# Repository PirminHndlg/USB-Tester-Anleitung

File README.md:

<h1>Anleitung zum USB Tester Löt Kit</h1>

<div class="img-container">
    
</div>

<h4>Enthaltene Komponenten</h4>
<ul>
    <li>1x pcb</li>
    <li>2x USB Typ-C Buchse (teilweise schon an pcb angelötet)</li>
    <li>1x USB Typ-A 3.0 Buchse</li>
    <li>1x Micro USB Typ-B Buchse</li>
    <li>1x Mini USB Typ-B Buchse</li>
    <li>1x USB Typ-B 3.0 Buchse</li>
    <li>1x Batterie Halterung</li>
    <li>30x Widerstand 2.2kΩ (25 + 5 Reserve)</li>
    <li>30x LEDs gelb (25 + 5 Reserve)</li>
    <li>1x Kondensator 10μF</li>
</ul>

<div class="img-container">
    
</div>

<p style="background-color: green; padding: 10px"><strong>Hinweis:</strong> Bei der USB-C Buchse auf der rechten Seite
    kann es sein, dass sich einige Pins untereinander brücken. Das ist kein Problem! Die Kontakte auf dem pcb sind
    sowieso mit einer VCC-Plane verbunden. Auf der linken Seite darf es aber nicht sein!</p>

<h4>Anleitung</h4>
<ol>
    <li>
        Löte die Widerstände und die LEDs auf die Platine, die oberen Kontakte sind für die Widerstände und die
        unteren für die LEDs
        <p style="background-color: red; padding: 10px"><strong>Wichtig:</strong> die LEDs haben eine Ausrichtung!</p>
        <div class="Website/img-container">
            
        </div>
        Auf der Rückseite der LED sieht man eine Markierung für die Kontakte. Der Kontakt mit dem Kreuz ist der Minuspol
        und muss an den linken Kontakt der Platine mit der vollständigen Umrandung gelötet werden.
        <div class="Website/img-container">
            
        </div>
        Auf der Vorderseite ist die Unterscheidung der beiden Kontakte der LEDs leider nur schwer zu erkennen, aber der
        Pluspol hat zwei kleine Streifen und der Minuspol nur einen.
        <br><br>
        12 LEDs + Widerstände sind für die linke Seite der Platine und 12 für die rechte Seite bestimmt. Das letze Paar
        kommt unten in die linke Ecke der Platine bei der Aufschrift "SHIELD".
    </li>
    <li>
        Löte die Buchsen auf die Platine. Anordnung siehe Bild. Für die Stecker auf der rechten Seite spielt es
        keine Rolle, ob einzelne Kontakte sich untereinander berühren und einen Kurzschluss bilden.
        <div class="img-container">

        </div>
        Falls die USB-C Buchsen noch nicht angelötet sind, ist das der schwierigste Teil. Ich war am erfolgreichsten,
        indem ich die mit Reflow-Löten angelötet habe.
        <p style="background-color: orange; padding: 10px"><strong>Hinweis:</strong> Bei der Micro-USB-B-Buche habe ich einen kleinen Fehler beim pcb gemacht. Diese muss sich das eine Bein mit einer USB-C-Buchse teilen. Gequetscht sollte aber alles nebeneinander passen.</p>
    </li>
    <li>
        Löte den Kondensator an die richtige Stelle neben dem Pluspol der Batterie. Die Ausrichtung spielt keine Rolle.
        <div class="img-container">
            
        </div>
    </li>
    <li>
        Löte die Batterie-Halterung an. Achte auf die richtige Polung! Es gibt eine kleine Markierung an der Ecke der
        Halterung für den Plus- und Minuspol.
    </li>
    <li>
        Und fertig ist dein USB Tester! Viel Spass beim Testen von USB-Kabeln!
    </li>
</ol>

<h3 style="background-color: red; text-align: center; padding: 10px; border-radius: 10px">Wie es auch überall steht, ist es wichtig, dass man
    den Tester <strong>nicht</strong> an ein Gerät anschließt,
    sondern nur Kabel!</h3>

<div class="img-container">
    
</div>

<h4>Weitere Links</h4>

<p><a href="https://github.com/PirminHndlg/USB-Tester-Anleitung/tree/main/Case">Hier</a> gibt eine 3D-Druck-Vorlage für
    ein kleines, einfaches Case.</p>

<p><a href="https://github.com/PirminHndlg/USB-Tester-Anleitung/tree/main/pcb">Hier</a> kann man das KiCad-Projekt zum
    pcb finden. Ich habe das <a href="https://github.com/alvarop/usb_c_cable_tester">Original von alvarop</a> etwas
    angepasst, da einzelne Teile nicht mehr verfügbar waren. Eine aktuelle Liste gibt es <a
            href="https://github.com/PirminHndlg/USB-Tester-Anleitung/blob/main/pcb/LCSC%20Exported%20May%2030%202024.csv">hier</a>
</p>

<h4>Erklärung zur Pin-Belegung</h4>

<div class="table-container">
    <table>
        <tr>
            <th>Charge only</th>
            <td>GND</td>
            <td>VBUS</td>
        </tr>
        <tr>
            <th>USB 2.0</th>
            <td>GND</td>
            <td>VBUS</td>
            <td>D-</td>
            <td>D+</td>
        </tr>
        <tr>
            <th>USB 3.0</th>
            <td>GND</td>
            <td>VBUS</td>
            <td>D-</td>
            <td>D+</td>
            <td>RX-</td>
            <td>RX+</td>
            <td>TX-</td>
            <td>TX+</td>
        </tr>
    </table>
</div>
<p>Bei USB-C als Host (Buchse auf linker Seite) und Client (Buchse auf rechter Seite) leuchten beide Seiten, da dann
    sowohl die A als auch die B Pins verbunden sind. Außerdem sollte mind. ein CC-Pin verbunden sein</p>

<div class="img-container">
    
</div>

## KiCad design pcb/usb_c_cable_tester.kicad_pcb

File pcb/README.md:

[gbr.zip](gbr.zip) für pcb-Bestellung

[components_lcsc.csv](components_lcsc.csv) enthält den Einkaufswagen bei LCSC für 50 USB-Tester

[kicad](kicad)-Ordner mit Kicad-Projekt

Kosten für 50 Stück: ca. 180€ (inkl. Versand) &#8594; unter 4€/Stück

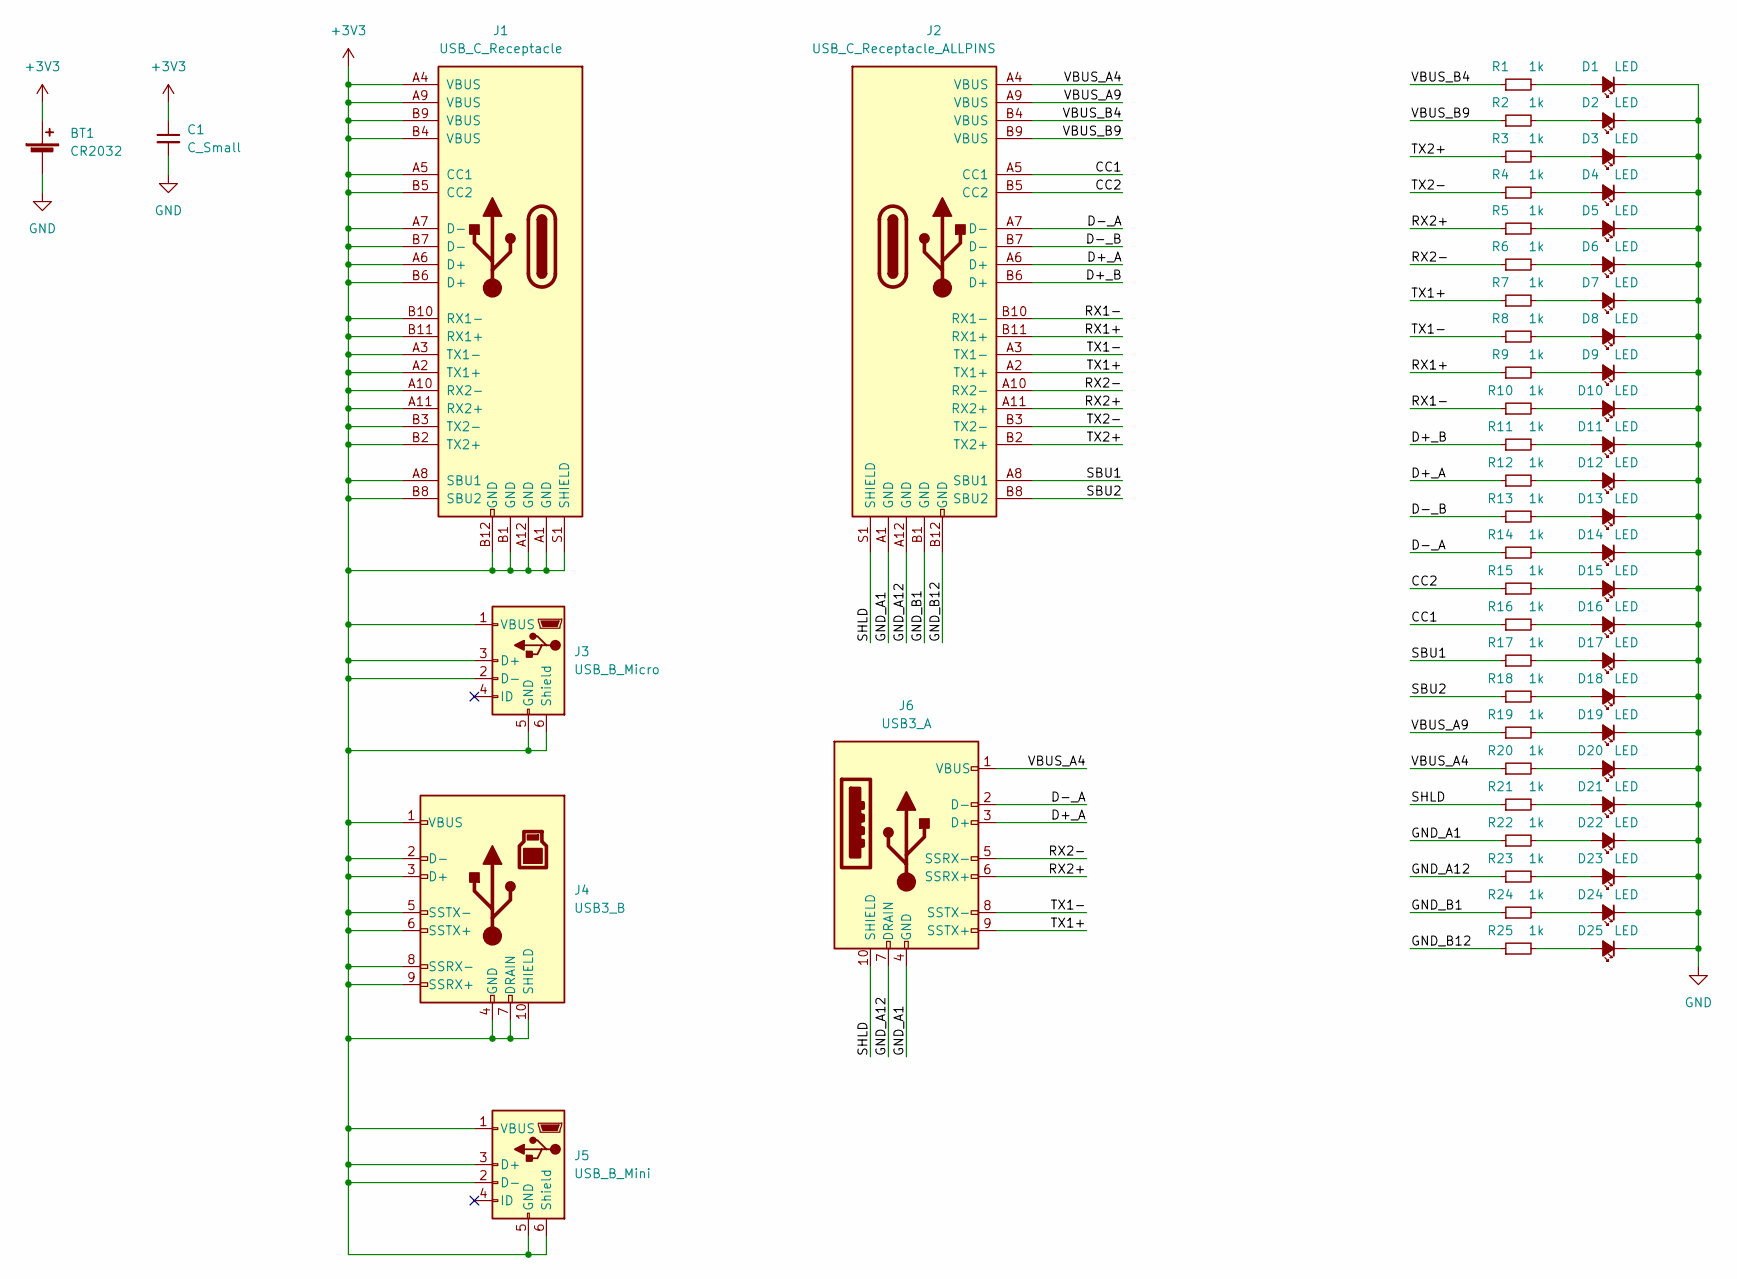
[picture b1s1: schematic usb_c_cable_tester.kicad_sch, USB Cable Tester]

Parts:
BT1: CR2032; BAT-TH_CR2032-BS-6-1; LCSC C70377
C1: C_Small; C_0805_2012Metric; LCSC C15850
D1, D2, D3, D4, D5, D6, D7, D8, D9, D10, D11, D12, D13, D14, D15, D16, D17, D18, D19, D20, D21, D22, D23, D24, D25: LED; LED_0603_1608Metric; LCSC C72038
J1: USB_C_Receptacle; USB_C; LCSC C456013
J2: USB_C_Receptacle_ALLPINS; USB_C; LCSC C456013
J3: USB_B_Micro; MICRO-USB-SMD_10118194-0001LF; LCSC C132563
J4: USB3_B; USB-B-TH_XUNPU_USB-306BWD-ARW; LCSC C2895032
J5: USB_B_Mini; MINI-USB-SMD_MINI-5PTP; LCSC C2681563
J6: USB3_A; USB-A-TH_U231-091N-5; LCSC C381137
R1, R2, R3, R4, R5, R6, R7, R8, R9, R10, R11, R12, R13, R14, R15, R16, R17, R18, R19, R20, R21, R22, R23, R24, R25: 1k; R_0603_1608Metric; LCSC C4190

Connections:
+3V3: BT1.1 (+), C1.1, J1.A1 (GND), J1.A2 (TX1+), J1.A3 (TX1-), J1.A4 (VBUS), J1.A5 (CC1), J1.A6 (D+), J1.A7 (D-), J1.A8 (SBU1), J1.A9 (VBUS), J1.A10 (RX2-), J1.A11 (RX2+), J1.A12 (GND), J1.B1 (GND), J1.B2 (TX2+), J1.B3 (TX2-), J1.B4 (VBUS), J1.B5 (CC2), J1.B6 (D+), J1.B7 (D-), J1.B8 (SBU2), J1.B9 (VBUS), J1.B10 (RX1-), J1.B11 (RX1+), J1.B12 (GND), J1.S1 (SHIELD), J3.1 (VBUS), J3.2 (D-), J3.3 (D+), J3.5 (GND), J3.6 (Shield), J4.1 (VBUS), J4.2 (D-), J4.3 (D+), J4.4 (GND), J4.5 (SSTX-), J4.6 (SSTX+), J4.7 (DRAIN), J4.8 (SSRX-), J4.9 (SSRX+), J4.10 (SHIELD), J5.1 (VBUS), J5.2 (D-), J5.3 (D+), J5.5 (GND), J5.6 (Shield)
/CC1: J2.A5 (CC1), R16.1
/CC2: J2.B5 (CC2), R15.1
/D+_A: J2.A6 (D+), J6.3 (D+), R12.1
/D+_B: J2.B6 (D+), R11.1
/D-_A: J2.A7 (D-), J6.2 (D-), R14.1
/D-_B: J2.B7 (D-), R13.1
/GND_A1: J2.A1 (GND), J6.4 (GND), R22.1
/GND_A12: J2.A12 (GND), J6.7 (DRAIN), R23.1
/GND_B1: J2.B1 (GND), R24.1
/GND_B12: J2.B12 (GND), R25.1
/RX1+: J2.B11 (RX1+), R9.1
/RX1-: J2.B10 (RX1-), R10.1
/RX2+: J2.A11 (RX2+), J6.6 (SSRX+), R5.1
/RX2-: J2.A10 (RX2-), J6.5 (SSRX-), R6.1
/SBU1: J2.A8 (SBU1), R17.1
/SBU2: J2.B8 (SBU2), R18.1
/SHLD: J2.S1 (SHIELD), J6.10 (SHIELD), R21.1
/TX1+: J2.A2 (TX1+), J6.9 (SSTX+), R7.1
/TX1-: J2.A3 (TX1-), J6.8 (SSTX-), R8.1
/TX2+: J2.B2 (TX2+), R3.1
/TX2-: J2.B3 (TX2-), R4.1
/VBUS_A4: J2.A4 (VBUS), J6.1 (VBUS), R20.1
/VBUS_A9: J2.A9 (VBUS), R19.1
/VBUS_B4: J2.B4 (VBUS), R1.1
/VBUS_B9: J2.B9 (VBUS), R2.1
GND: BT1.2 (-), C1.2, D1.1 (K), D2.1 (K), D3.1 (K), D4.1 (K), D5.1 (K), D6.1 (K), D7.1 (K), D8.1 (K), D9.1 (K), D10.1 (K), D11.1 (K), D12.1 (K), D13.1 (K), D14.1 (K), D15.1 (K), D16.1 (K), D17.1 (K), D18.1 (K), D19.1 (K), D20.1 (K), D21.1 (K), D22.1 (K), D23.1 (K), D24.1 (K), D25.1 (K)
unnamed: D1.2 (A), R1.2
unnamed: D2.2 (A), R2.2
unnamed: D3.2 (A), R3.2
unnamed: D4.2 (A), R4.2
unnamed: D5.2 (A), R5.2
unnamed: D6.2 (A), R6.2
unnamed: D7.2 (A), R7.2
unnamed: D8.2 (A), R8.2
unnamed: D9.2 (A), R9.2
unnamed: D10.2 (A), R10.2
unnamed: D11.2 (A), R11.2
unnamed: D12.2 (A), R12.2
unnamed: D13.2 (A), R13.2
unnamed: D14.2 (A), R14.2
unnamed: D15.2 (A), R15.2
unnamed: D16.2 (A), R16.2
unnamed: D17.2 (A), R17.2
unnamed: D18.2 (A), R18.2
unnamed: D19.2 (A), R19.2
unnamed: D20.2 (A), R20.2
unnamed: D21.2 (A), R21.2
unnamed: D22.2 (A), R22.2
unnamed: D23.2 (A), R23.2
unnamed: D24.2 (A), R24.2
unnamed: D25.2 (A), R25.2

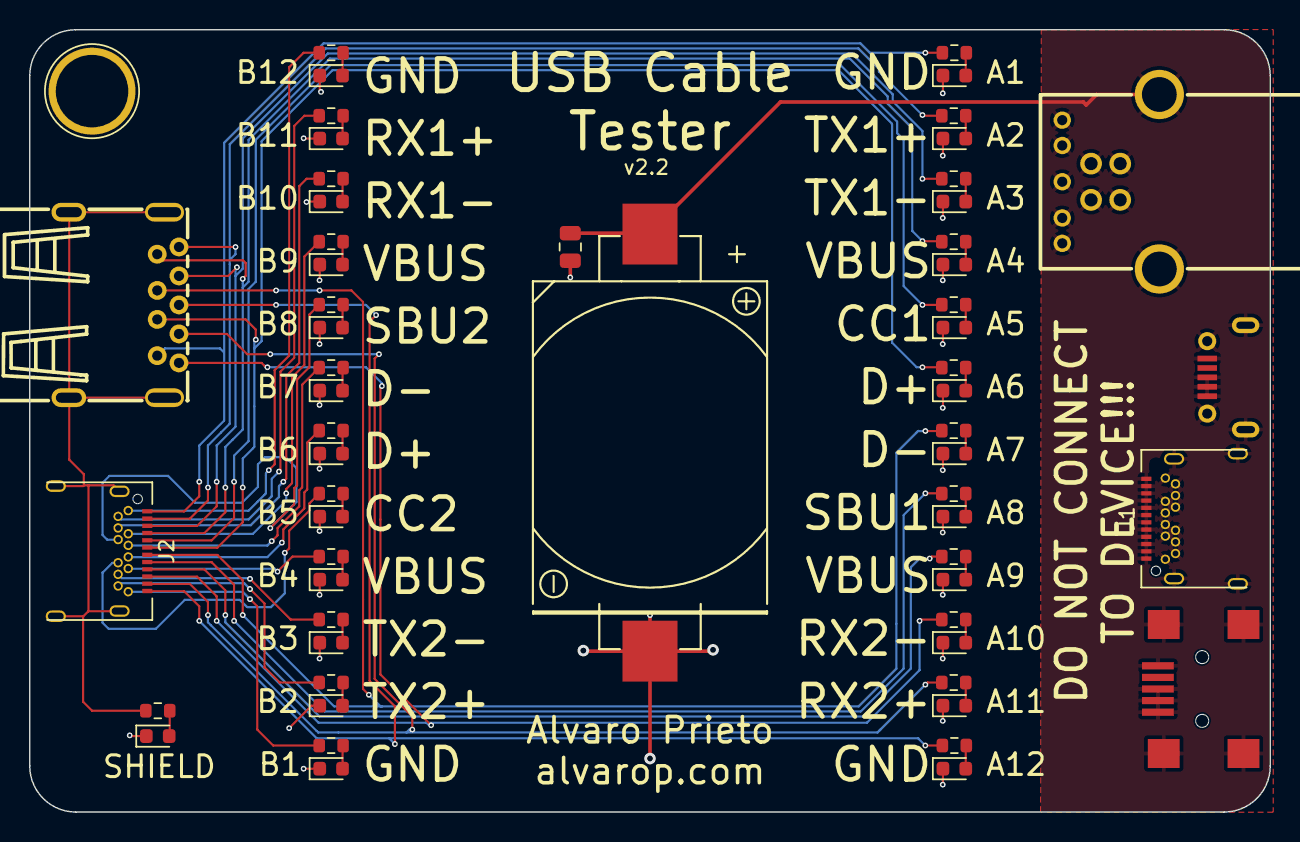
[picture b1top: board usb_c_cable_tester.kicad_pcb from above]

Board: 2 copper layers, 85.6 x 54.0 mm, 58 parts (0 on the bottom side), 52 nets.

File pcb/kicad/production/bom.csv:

Designator,Footprint,Quantity,Value,LCSC Part #
BT1,BAT-TH_CR2032-BS-6-1,1,CR2032,C70377
C1,0805,1,C_Small,C15850
"D1, D10, D11, D12, D13, D14, D15, D16, D17, D18, D19, D2, D20, D21, D22, D23, D24, D25, D3, D4, D5, D6, D7, D8, D9",0603,25,LED,C72038
J1,USB_C,1,USB_C_Receptacle,C456013
J2,USB_C,1,USB_C_Receptacle_ALLPINS,C456013
J3,MICRO-USB-SMD_10118194-0001LF,1,USB_B_Micro,C132563
J4,USB-B-TH_XUNPU_USB-306BWD-ARW,1,USB3_B,C2895032
J5,MINI-USB-SMD_MINI-5PTP,1,USB_B_Mini,C2681563
J6,USB-A-TH_U231-091N-5,1,USB3_A,C381137
"R1, R10, R11, R12, R13, R14, R15, R16, R17, R18, R19, R2, R20, R21, R22, R23, R24, R25, R3, R4, R5, R6, R7, R8, R9",0603,25,1k,C4190

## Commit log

2024-05-30 added all files
2024-05-30 made folder for Website
2024-05-30 without c html file
2024-05-30 Case files
2024-05-30 added pcb design
2024-05-30 csv of componentes
2024-05-30 renamed files
2024-05-30 img optim
2024-05-30 not needed
2024-06-01 some more infos for gnd plane
2024-06-01 gnd -> vcc
2024-06-01 rechts links schwäche
2024-06-14 with info for usb c and micro usb b
2024-12-08 changes (and a bit chaos)
2024-12-08 moved files to kicad folder
2024-12-08 removed not needed files
2024-12-08 added gitignore
2024-12-08 added files to gitignore
2024-12-08 chaos and added components file for ordering at lcsc
2025-10-27 Add files for pcb production and flyer file
